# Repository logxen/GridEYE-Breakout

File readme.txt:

OVERVIEW

This is a breakout board for the Panasonic Grid-EYE AMG88xx line of thermopile arrays. The sensors are available in both 3.3v and 5v flavors and capture 8 by 8 pixels of far ir data.

The demo firmware is an Arduino sketch and runs on an arduino. (http://arduino.cc/) It probably requires at v1.0 ide. Check out Arduino docs for how to wire an i2c device.

The demo software is a Processing sketch. (http://processing.org/) Processing is what the Arduino ide is based on and I feel that they make a nice set. It expects to connect to the arduino via a serial port. You will need to manually set the serial port in the source file.

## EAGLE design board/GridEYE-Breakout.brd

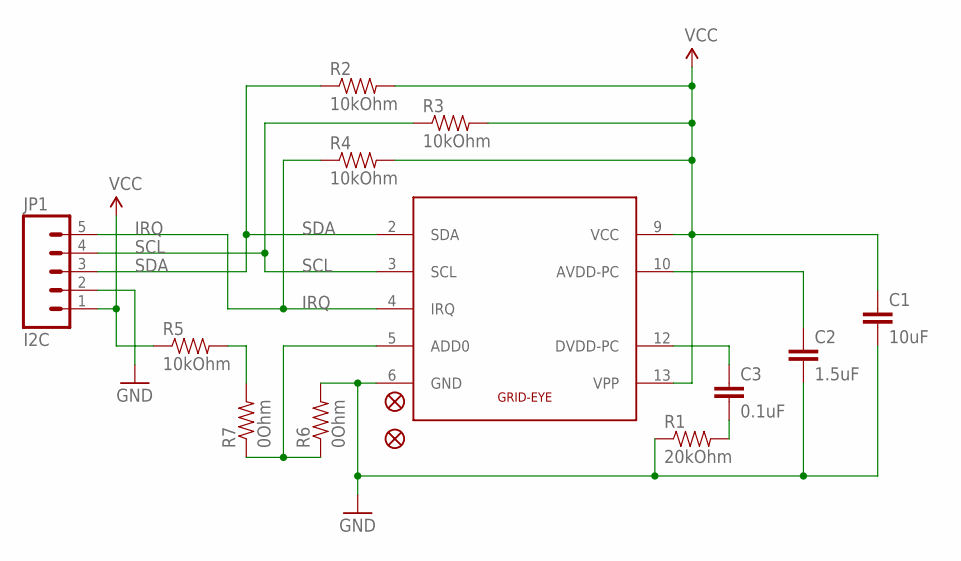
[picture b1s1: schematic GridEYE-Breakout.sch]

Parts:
C1: 10uF; 0603-CAP
C2: 1.5uF; 0603-CAP
C3: 0.1uF; 0603-CAP
JP1: I2C; 1X05
JP2, JP3: FIDUCIAL1X2; FIDUCIAL-1X2
R1: 20kOhm; 0603-RES
R2, R3, R4, R5: 10kOhm; 0603-RES
R6, R7: 0Ohm; 0402-RES
U1: GRID-EYE

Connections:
ADD0: R6.1, R7.1, U1.5 (ADD0)
AVDD: C2.1, U1.10 (AVDD-PC)
DVDD: C3.1, U1.12 (DVDD-PC)
GND: C1.2, C2.2, JP1.2, R1.1, R6.2, U1.6 (GND)
IRQ: JP1.5, R4.1, U1.4 (IRQ)
unnamed: R5.2, R7.2
unnamed: C3.2, R1.2
SCL: JP1.4, R3.1, U1.3 (SCL)
SDA: JP1.3, R2.1, U1.2 (SDA)
VCC: C1.1, JP1.1, R2.2, R3.2, R4.2, R5.1, U1.9 (VCC), U1.13 (VPP)

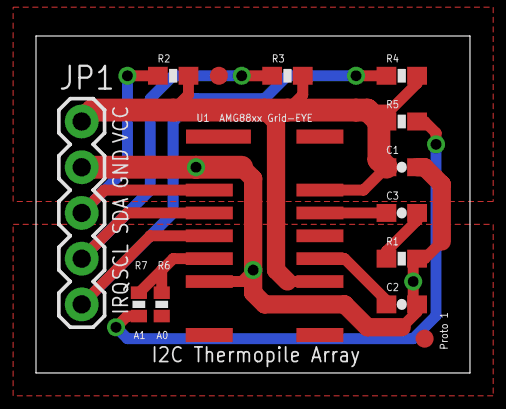
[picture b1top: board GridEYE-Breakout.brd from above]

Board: 2 copper layers, 24.1 x 18.7 mm, 14 parts (0 on the bottom side), 10 nets.

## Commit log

2012-12-01 Initial commit of prototype 1
2013-09-16 Added demo firmware and software
2017-10-03 Update Grid_EYE_Breakout.pde
    updated the size - > surface.setSize for Processing 3

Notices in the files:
parts and their libraries:
SparkFun-Capacitors: Licensing: CC v3.0 Share-Alike You are welcome to use this library for commercial purposes.
